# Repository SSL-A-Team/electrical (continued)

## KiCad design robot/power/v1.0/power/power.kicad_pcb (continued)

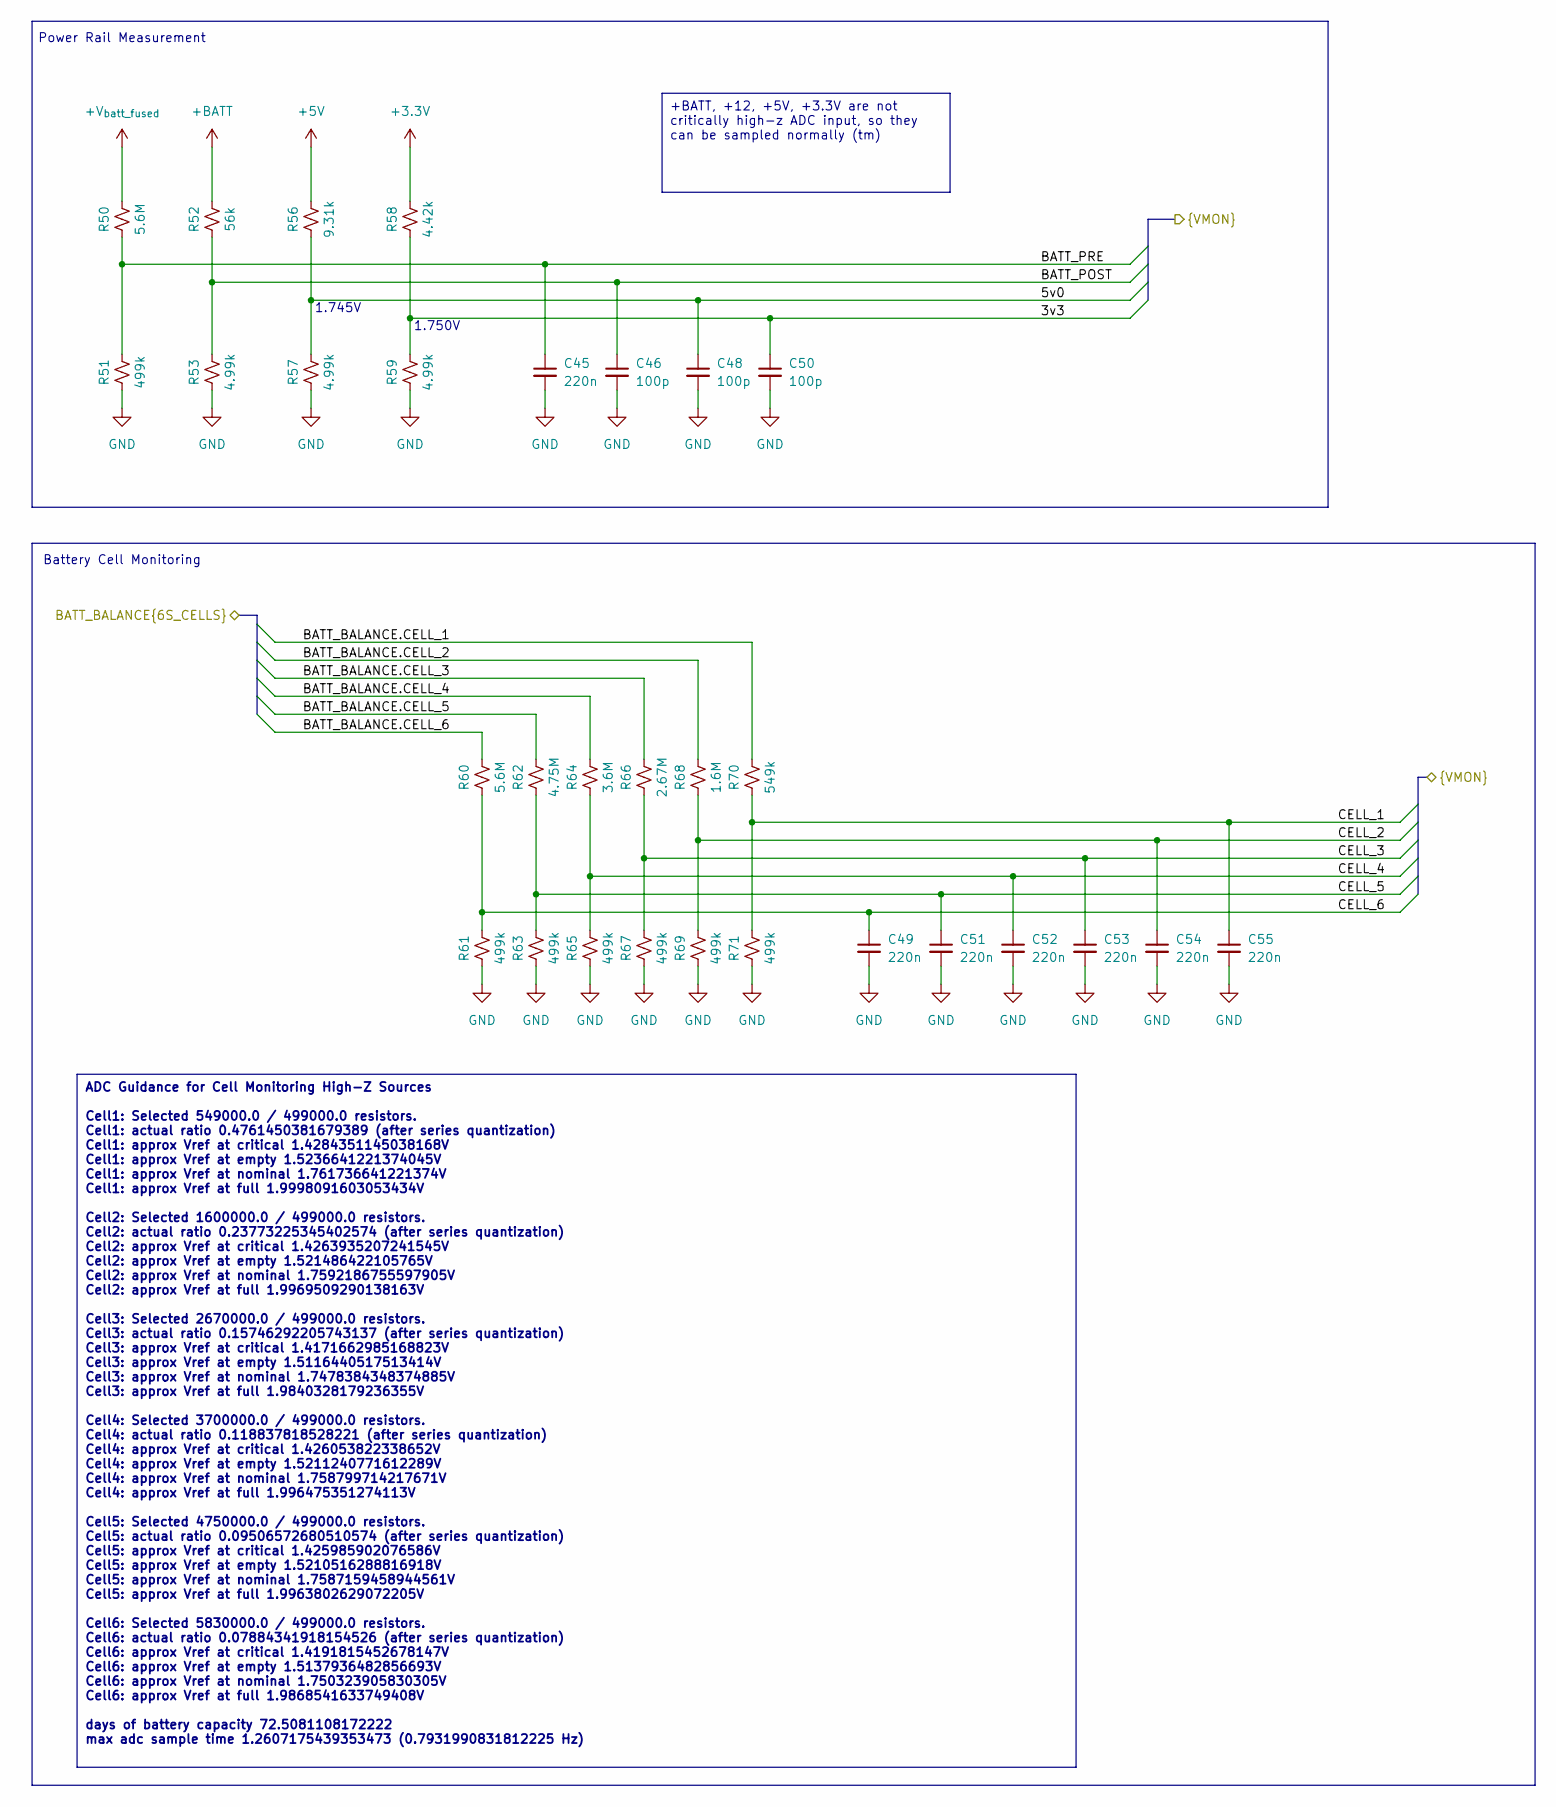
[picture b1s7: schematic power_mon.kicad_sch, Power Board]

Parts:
C45, C49, C51, C52, C53, C54, C55: 220n; C_0402_1005Metric
C46, C48, C50: 100p; C_0402_1005Metric
R50, R60: 5.6M; R_0402_1005Metric
R51, R61, R63, R65, R67, R69, R71: 499k; R_0402_1005Metric
R52: 56k; R_0402_1005Metric
R53, R57, R59: 4.99k; R_0402_1005Metric
R56: 9.31k; R_0402_1005Metric
R58: 4.42k; R_0402_1005Metric
R62: 4.75M; R_0402_1005Metric
R64: 3.6M; R_0402_1005Metric
R66: 2.67M; R_0402_1005Metric
R68: 1.6M; R_0402_1005Metric
R70: 549k; R_0402_1005Metric

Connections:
+3.3V: R58.1; also elsewhere on the board
+5V: R56.1; also elsewhere on the board
+BATT: R52.1; also elsewhere on the board
+V_{batt_fused}: R50.1; also elsewhere on the board
/input_connectors/BATT_BALANCE.CELL_1: R70.1; also elsewhere on the board
/input_connectors/BATT_BALANCE.CELL_2: R68.1; also elsewhere on the board
/input_connectors/BATT_BALANCE.CELL_3: R66.1; also elsewhere on the board
/input_connectors/BATT_BALANCE.CELL_4: R64.1; also elsewhere on the board
/input_connectors/BATT_BALANCE.CELL_5: R62.1; also elsewhere on the board
/input_connectors/BATT_BALANCE.CELL_6: R60.1; also elsewhere on the board
/mcu/3v3: C50.1, R58.2, R59.1; also elsewhere on the board
/mcu/5v0: C48.1, R56.2, R57.1; also elsewhere on the board
/mcu/BATT_POST: C46.1, R52.2, R53.1; also elsewhere on the board
/mcu/BATT_PRE: C45.1, R50.2, R51.1; also elsewhere on the board
/mcu/CELL_1: C55.1, R70.2, R71.1; also elsewhere on the board
/mcu/CELL_2: C54.1, R68.2, R69.1; also elsewhere on the board
/mcu/CELL_3: C53.1, R66.2, R67.1; also elsewhere on the board
/mcu/CELL_4: C52.1, R64.2, R65.1; also elsewhere on the board
/mcu/CELL_5: C51.1, R62.2, R63.1; also elsewhere on the board
/mcu/CELL_6: C49.1, R60.2, R61.1; also elsewhere on the board
GND: C45.2, C46.2, C48.2, C49.2, C50.2, C51.2, C52.2, C53.2, C54.2, C55.2, R51.2, R53.2, R57.2, R59.2, R61.2, R63.2, R65.2, R67.2, R69.2, R71.2; also elsewhere on the board

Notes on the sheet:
+BATT, +12, +5V, +3.3V are not critically high-z ADC input, so they can be sampled normally (tm)
ADC Guidance for Cell Monitoring High-Z Sources Cell1: Selected 549000.0 / 499000.0 resistors. Cell1: actual ratio 0.4761450381679389 (after series quantization) Cell1: approx Vref at critical 1.4284351145038168V Cell1: approx Vref at empty 1.5236641221374045V Cell1: approx Vref at nominal 1.761736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
1.745V
Power Rail Measurement
Battery Cell Monitoring
1.750V

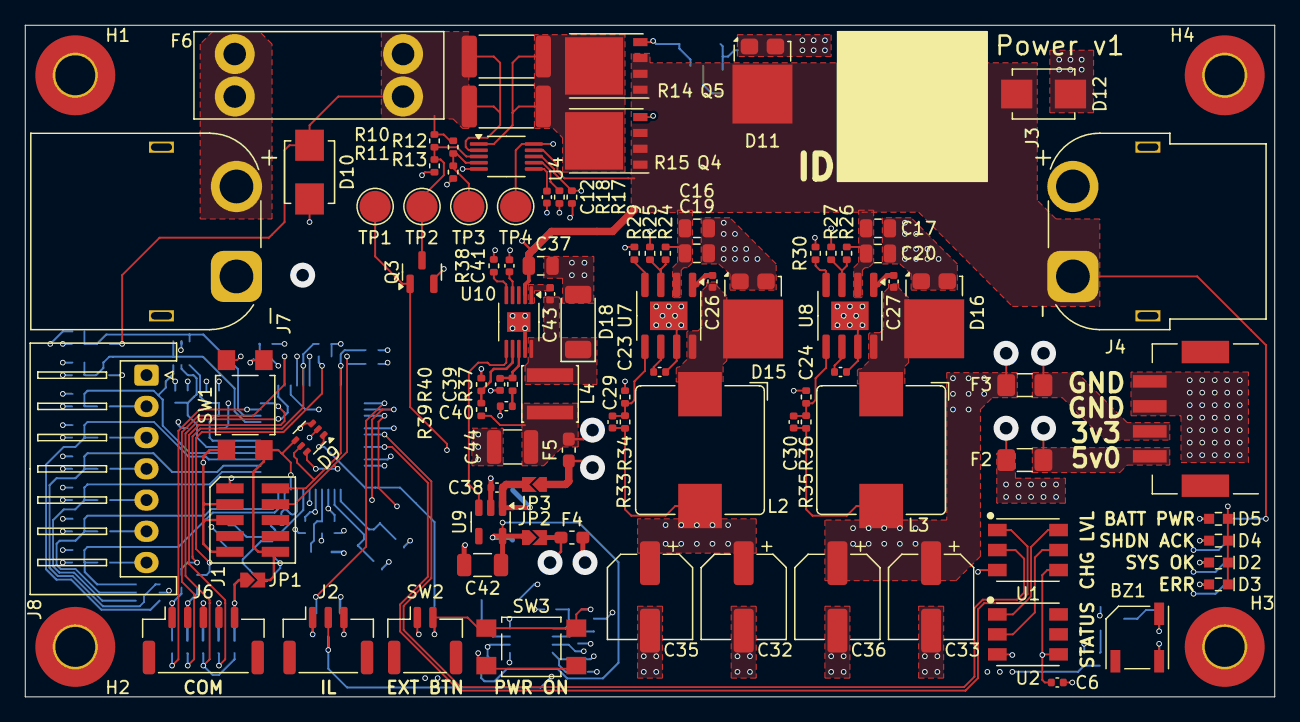
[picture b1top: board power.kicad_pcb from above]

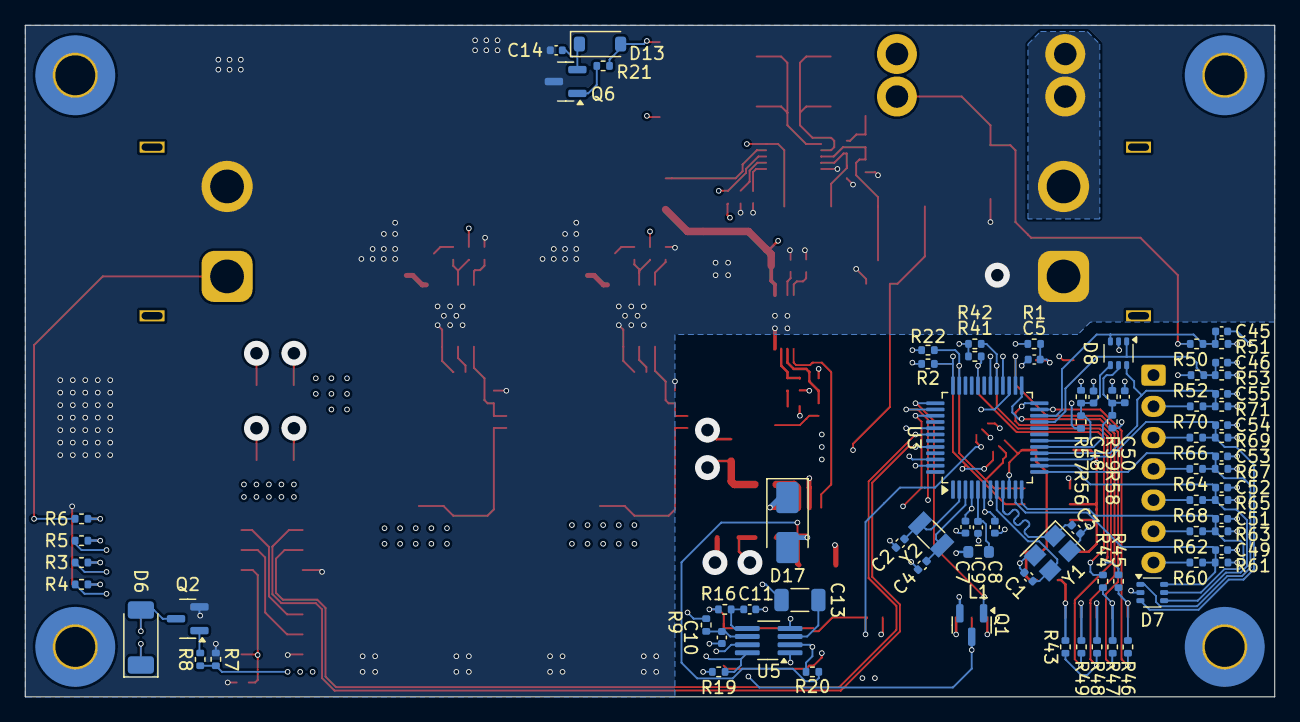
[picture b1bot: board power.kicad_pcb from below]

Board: 6 copper layers, 100.0 x 53.8 mm, 175 parts (78 on the bottom side), 101 nets.

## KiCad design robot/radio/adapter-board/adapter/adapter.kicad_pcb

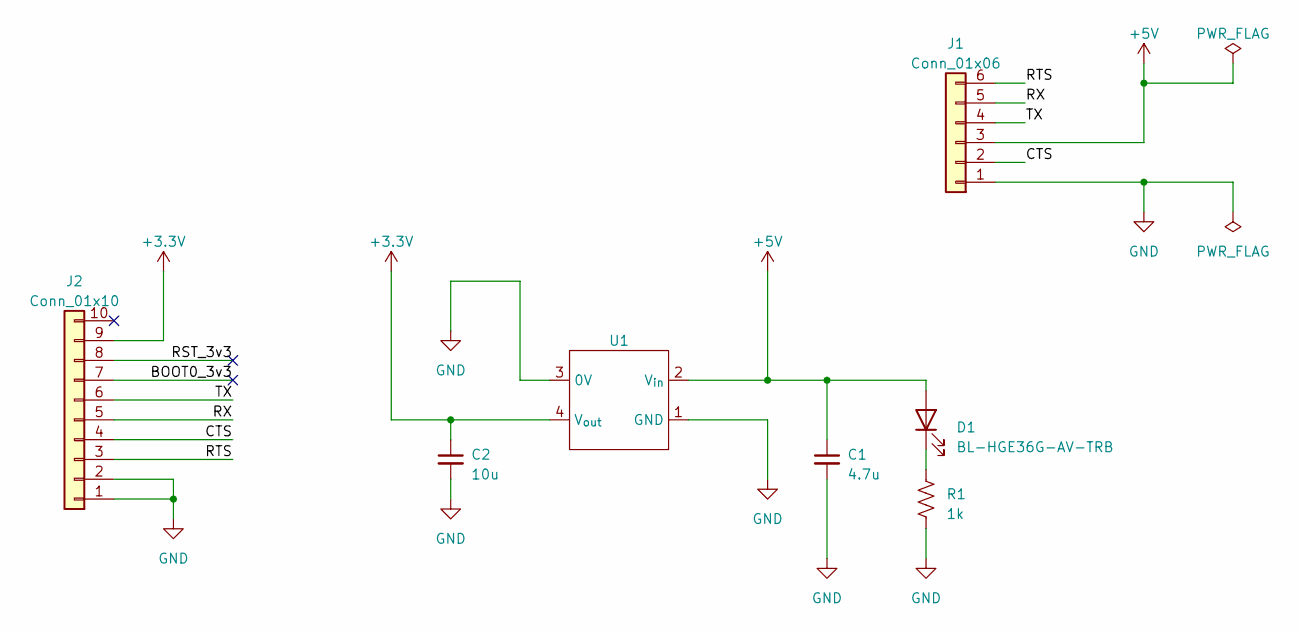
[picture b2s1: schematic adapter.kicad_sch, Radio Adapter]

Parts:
C1: 4.7u; C_0603_1608Metric
C2: 10u; C_0603_1608Metric
D1: BL-HGE36G-AV-TRB; D_0603_1608Metric
J1: Conn_01x06; PinHeader_1x06_P2.54mm_Horizontal
J2: Conn_01x10; JST_SH_SM10B-SRSS-TB_1x10-1MP_P1.00mm_Horizontal
R1: 1k; R_0603_1608Metric
U1: B0503S-1WR3

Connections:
+3.3V: C2.1, J2.9, U1.4 (V_{out})
+5V: C1.1, D1.2 (A), J1.3, U1.2 (V_{in})
/BOOT0_3v3: J2.7
/CTS: J1.2, J2.4
/RST_3v3: J2.8
/RTS: J1.6, J2.3
/RX: J1.5, J2.5
/TX: J1.4, J2.6
GND: C1.2, C2.2, J1.1, J2.1, J2.2, R1.1, U1.1 (GND), U1.3 (0V)
unnamed: D1.1 (K), R1.2

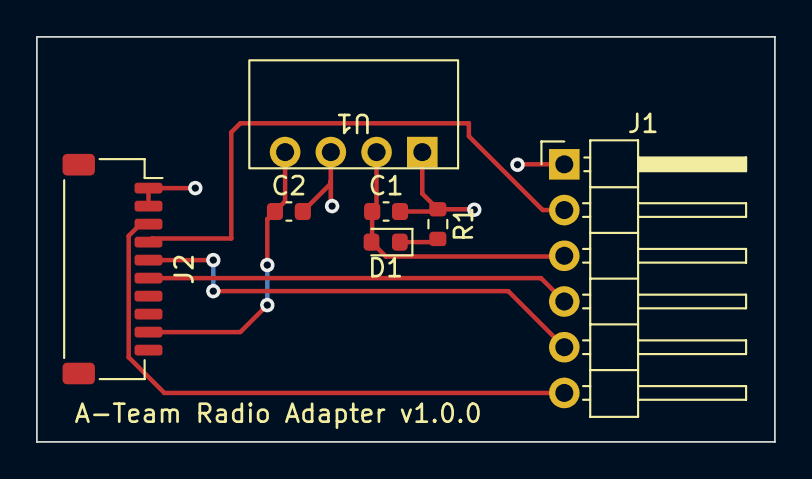
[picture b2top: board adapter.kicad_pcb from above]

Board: 2 copper layers, 41.0 x 22.5 mm, 7 parts (0 on the bottom side), 8 nets.

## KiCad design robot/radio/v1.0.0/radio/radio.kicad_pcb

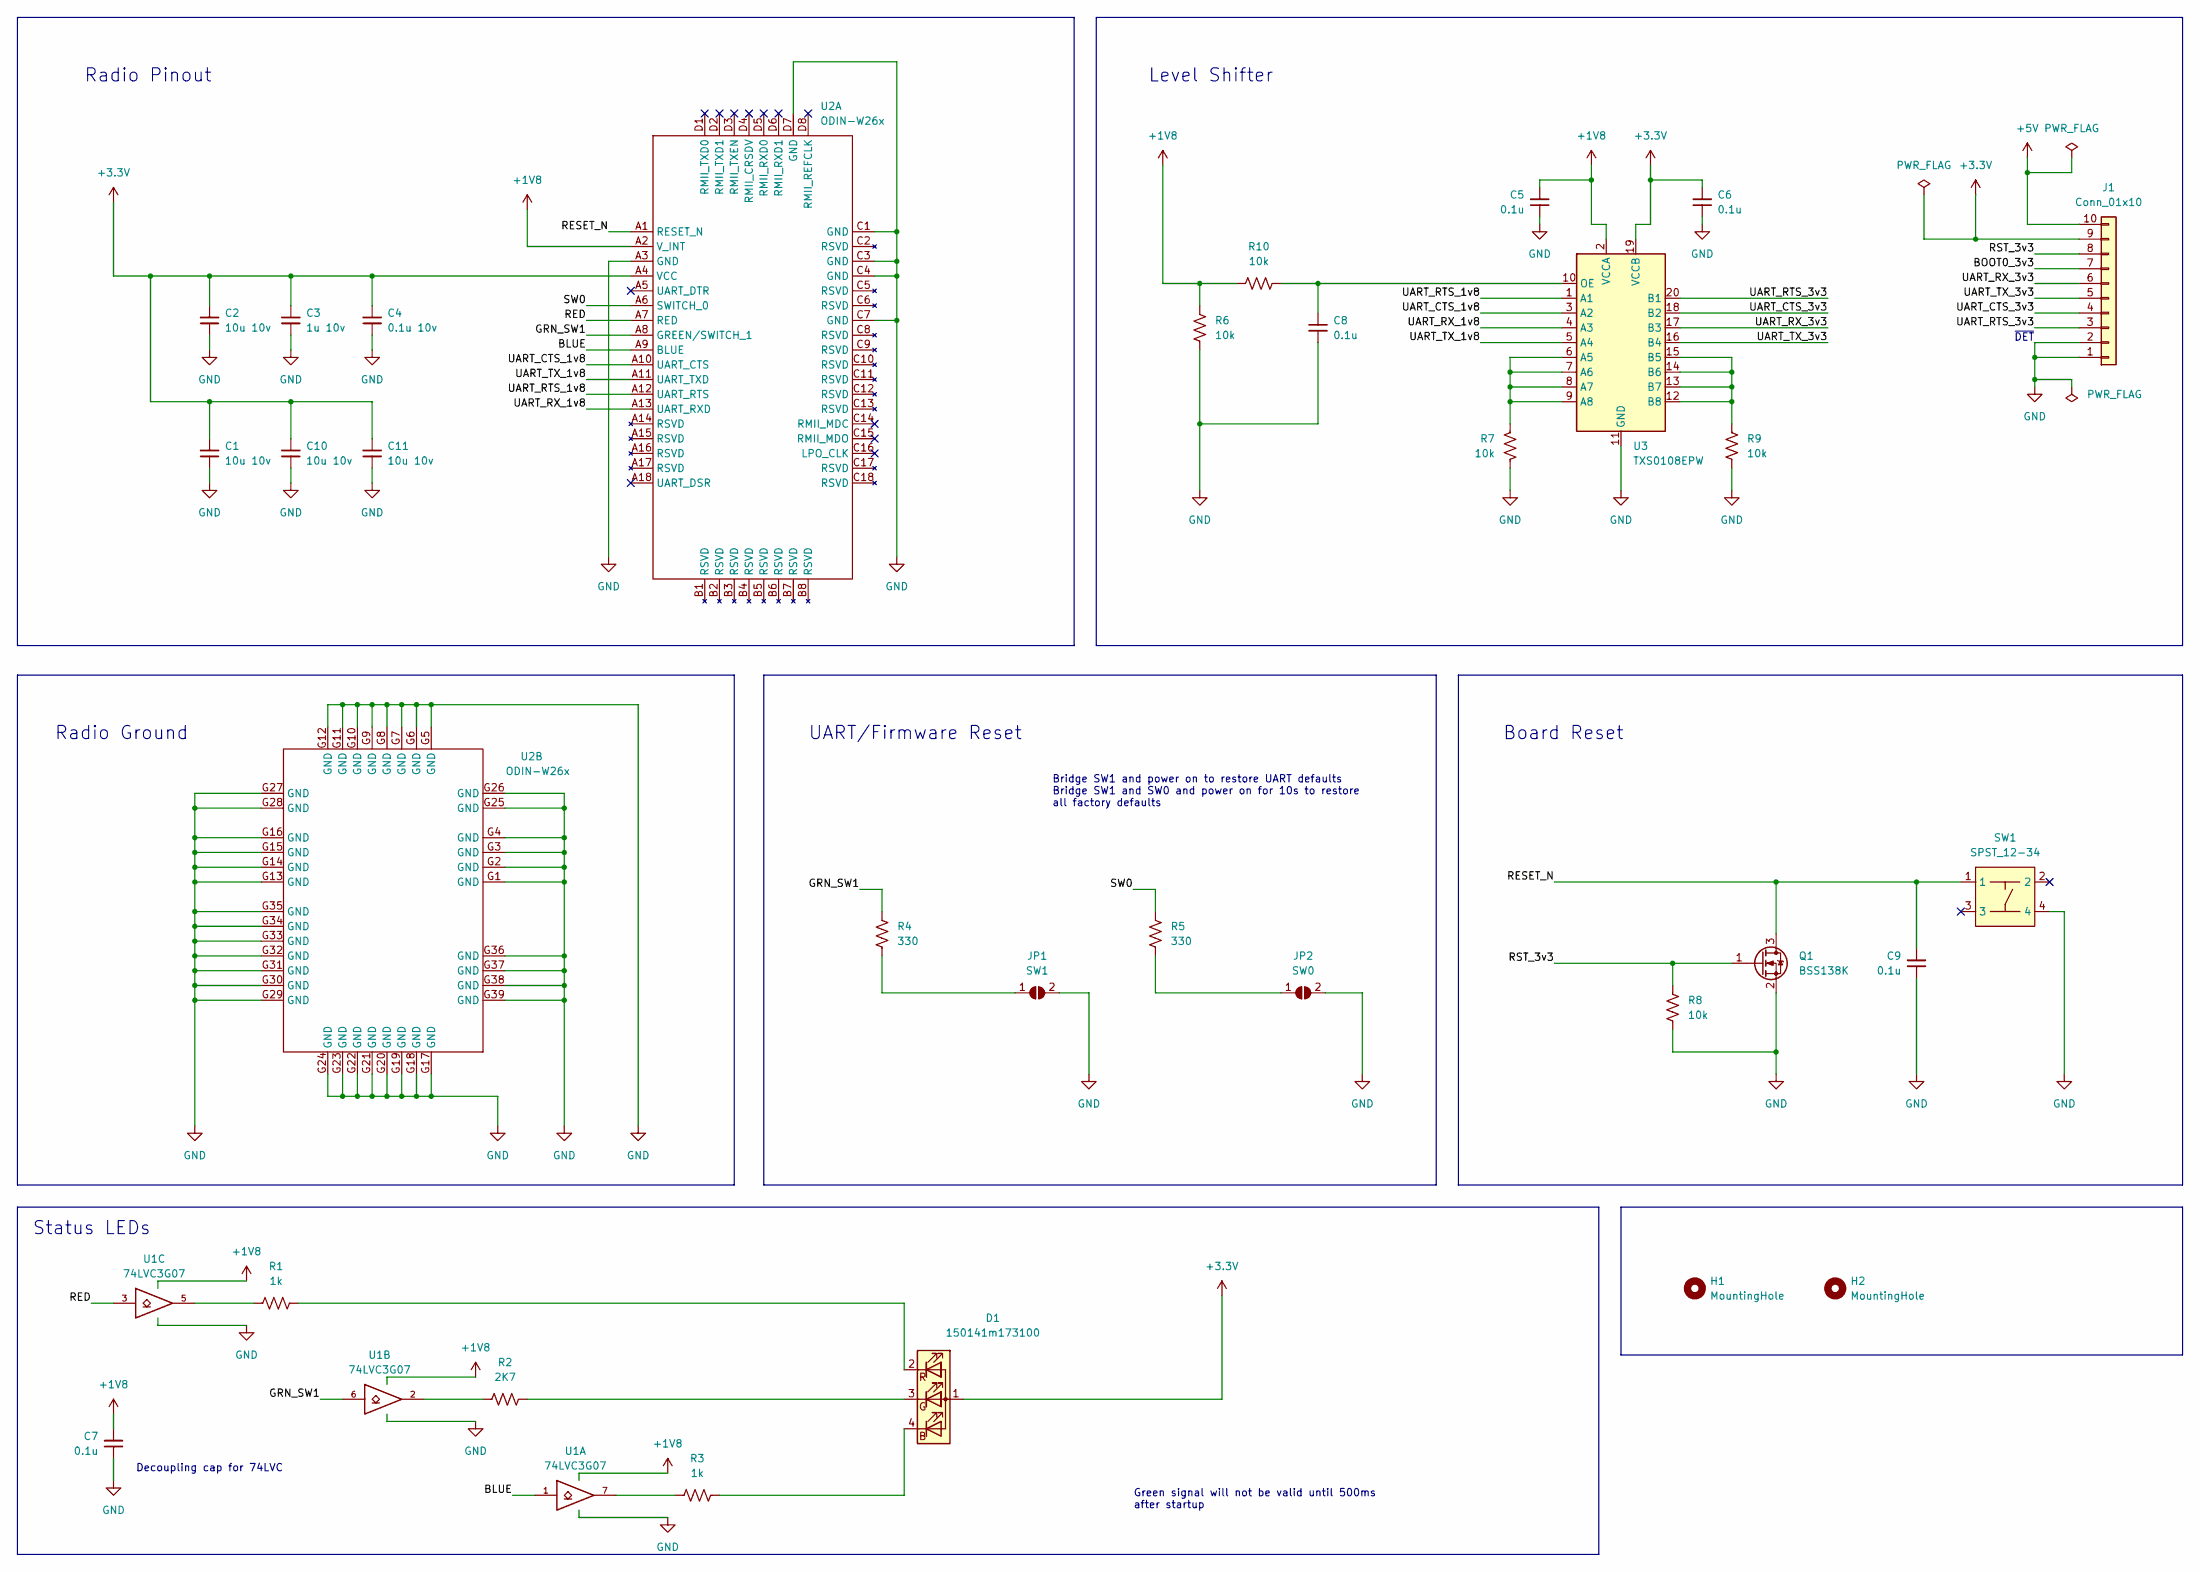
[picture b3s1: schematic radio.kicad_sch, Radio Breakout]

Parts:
C1, C2, C10, C11: 10u 10v; C_0603_1608Metric
C3: 1u 10v; C_0603_1608Metric
C4: 0.1u 10v; C_0603_1608Metric
C5, C6, C7, C8, C9: 0.1u; C_0603_1608Metric
D1: 150141m173100; Wurth_Elektronik_150141M173100
H1, H2: MountingHole; MountingHole_3.2mm_M3
J1: Conn_01x10; JST_SH_SM10B-SRSS-TB_1x10-1MP_P1.00mm_Horizontal
JP1: SW1; SolderJumper-3_P2.0mm_Open_TrianglePad1.0x1.5mm
JP2: SW0; SolderJumper-3_P2.0mm_Open_TrianglePad1.0x1.5mm
Q1: BSS138K; SOT-23
R1, R3: 1k; R_0603_1608Metric
R2: 2K7; R_0603_1608Metric
R4, R5: 330; R_0603_1608Metric
R6, R7, R8, R9, R10: 10k; R_0603_1608Metric
SW1: SPST_12-34; TS02-66-73-BK-160-SCR-D
U1: 74LVC3G07; VSSOP-8_2.3x2mm_P0.5mm
U2: ODIN-W26x; ODIN_W2
U3: TXS0108EPW; TSSOP-20_4.4x6.5mm_P0.65mm

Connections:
+1V8: C5.2, C7.2, R6.2, R10.2, U1.8 (VCC), U2.A2 (V_INT), U3.2 (VCCA)
+3V3: C1.2, C2.2, C3.2, C4.2, C6.2, C10.2, C11.2, D1.1 (A), J1.9, U2.A4 (VCC), U3.19 (VCCB)
+5V: J1.10
/BLUE: U1.1, U2.A9 (BLUE)
/BOOT0_3v3: J1.7
/GRN_SW1: R4.2, U1.6, U2.A8 (GREEN/SWITCH_1)
/RED: U1.3, U2.A7 (RED)
/RESET_N: C9.2, Q1.3 (D), SW1.1, U2.A1 (RESET_N)
/RST_3v3: J1.8, Q1.1 (G), R8.2
/SW0: R5.1, U2.A6 (SWITCH_0)
/UART_CTS_1v8: U2.A10 (UART_CTS), U3.3 (A2)
/UART_CTS_3v3: J1.4, U3.18 (B2)
/UART_RTS_1v8: U2.A12 (UART_RTS), U3.1 (A1)
/UART_RTS_3v3: J1.3, U3.20 (B1)
/UART_RX_1v8: U2.A13 (UART_RXD), U3.4 (A3)
/UART_RX_3v3: J1.6, U3.17 (B3)
/UART_TX_1v8: U2.A11 (UART_TXD), U3.5 (A4)
/UART_TX_3v3: J1.5, U3.16 (B4)
GND: C1.1, C2.1, C3.1, C4.1, C5.1, C6.1, C7.1, C8.2, C9.1, C10.1, C11.1, J1.1, J1.2, JP1.2 (B), JP2.2 (B), Q1.2 (S), R6.1, R7.1, R8.1, R9.1, SW1.4, U1.4 (GND), U2.A3 (GND), U2.C1 (GND), U2.C3 (GND), U2.C4 (GND), U2.C7 (GND), U2.D7 (GND), U2.G1 (GND), U2.G2 (GND), U2.G3 (GND), U2.G4 (GND), U2.G5 (GND), U2.G6 (GND), U2.G7 (GND), U2.G8 (GND), U2.G9 (GND), U2.G10 (GND), U2.G11 (GND), U2.G12 (GND), U2.G13 (GND), U2.G14 (GND), U2.G15 (GND), U2.G16 (GND), U2.G17 (GND), U2.G18 (GND), U2.G19 (GND), U2.G20 (GND), U2.G21 (GND), U2.G22 (GND), U2.G23 (GND), U2.G24 (GND), U2.G25 (GND), U2.G26 (GND), U2.G27 (GND), U2.G28 (GND), U2.G29 (GND), U2.G30 (GND), U2.G31 (GND), U2.G32 (GND), U2.G33 (GND), U2.G34 (GND), U2.G35 (GND), U2.G36 (GND), U2.G37 (GND), U2.G38 (GND), U2.G39 (GND), U3.11 (GND)
unnamed: D1.2 (RK), R1.2
unnamed: D1.3 (GK), R2.2
unnamed: D1.4 (BK), R3.2
unnamed: JP1.1 (A), R4.1
unnamed: JP2.1 (A), R5.2
unnamed: R1.1, U1.5
unnamed: R2.1, U1.2
unnamed: R3.1, U1.7
unnamed: R7.2, U3.6 (A5), U3.7 (A6), U3.8 (A7), U3.9 (A8)
unnamed: R9.2, U3.12 (B8), U3.13 (B7), U3.14 (B6), U3.15 (B5)
unnamed: C8.1, R10.1, U3.10 (OE)

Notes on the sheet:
Radio Ground
~{DET}
Radio Pinout
Green signal will not be valid until 500ms after startup
Level Shifter
Board Reset
Decoupling cap for 74LVC
Status LEDs
UART/Firmware Reset
Bridge SW1 and power on to restore UART defaults Bridge SW1 and SW0 and power on for 10s to restore all factory defaults

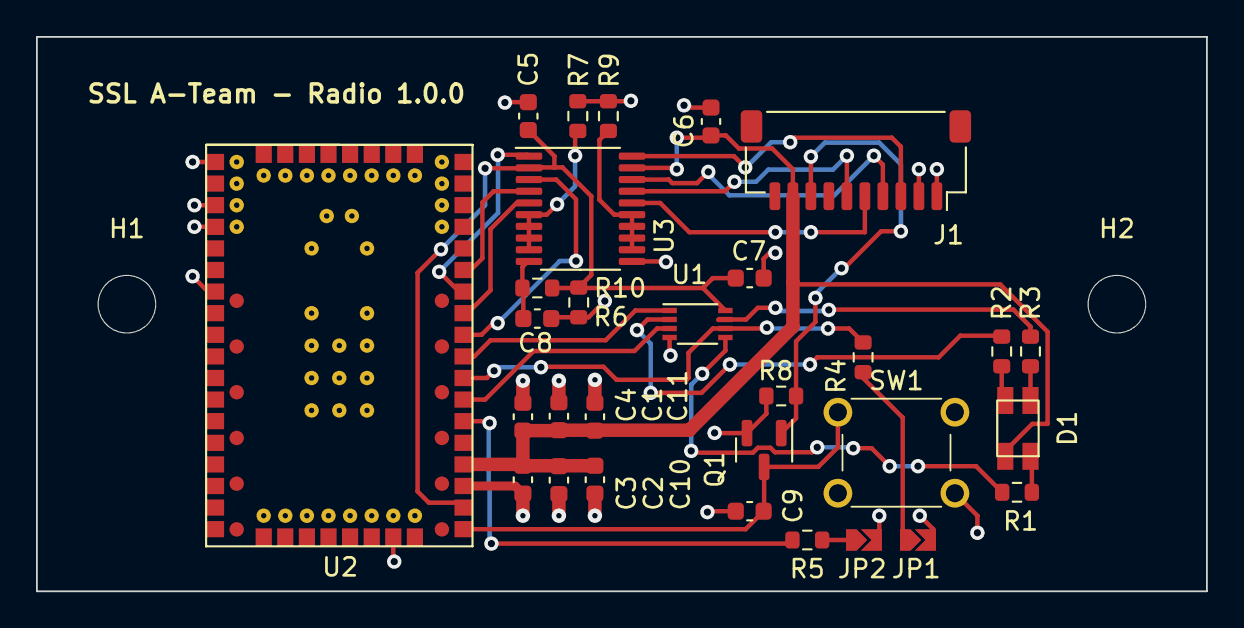
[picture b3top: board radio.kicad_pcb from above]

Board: 2 copper layers, 65.0 x 30.8 mm, 32 parts (0 on the bottom side), 28 nets.
